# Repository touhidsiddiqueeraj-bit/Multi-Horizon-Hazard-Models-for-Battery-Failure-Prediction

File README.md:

# Multi-Horizon Failure-Risk Models for Battery Failure Prediction

Multi-horizon failure-risk classification for lithium-ion cells: instead of
remaining-useful-life regression, predict whether a cell fails within the next
H cycles. The study's central contribution is a **validity analysis** — apparent
cross-dataset, cross-chemistry transfer is largely a **State-of-Health (SOH)
shortcut**, reproducible by an unfitted threshold rule, not transferable
degradation knowledge. Plus a complete ESP32-S3 embedded deployment.

> **Status.** The deliverable paper is `paper_ieee_access/main_access.pdf`
> (IEEE Access, generated — see [Paper build](#paper-build)). A condensed
> Journal of Energy Storage submission package lives in `paper_jest/`
> (manuscript + supplement). An IEEE Transactions on Reliability submission
> package lives in `paper_tr/` (manuscript, supplement, cover letter,
> checklist, author info). Numbers below are headline values; every number
> in the paper is generated from `results_v2/` — see [Reproduction](#reproduction).

---

## Headline results

- **Within-dataset:** fold-mean AUC 0.90–0.96 across tree ensembles (XGBoost,
  LightGBM, Random Forest) under cell-disjoint evaluation with leakage-free
  (cross-fitted out-of-fold) calibration.
- **SOH ablation (transfer):** ALL-LCO → Severson (141 LFP cells) at H=20 —
  pooled AUC **0.896 with SOH → 0.750 without** (XGBoost); the SOH
  distance-to-threshold rule alone reaches 0.912.
- **Diagnosis vs prognosis:** the label window includes the scoring cycle, so
  with-SOH numbers mix concurrent detection with prediction. Restricting to
  rows scored while SOH > 0.80 gives **0.838** on Severson — the remainder is
  near-threshold ranking, priced by the failure-definition ablation
  (voltage-sag-only relabeling cuts with-SOH transfer 0.90 → 0.72).
- **Battery Archive replication (60 new cells, pre-registered):** with-SOH
  transfer spans 0.77–1.00 pooled AUC, collapsing to 0.36–0.91 outside the
  single-condition HNEI NMC group, where full no-SOH transfer stays ≈0.99
  (narrow stereotyped protocols transfer; diverse ones do not).
- **Calibration:** Platt preserves discrimination best at comparable error;
  isotonic fails under shift; target recalibration repairs ECE but not ranking.
- **Deployment:** three ensembles (900 trees, 26,336 nodes) in a ~372 kB flat
  binary on a $12 ESP32-S3 — under 1 ms per inference for a single
  SRAM-resident model, reproducing `predict_proba()` to within 1.1×10⁻⁶.

Because SOH enters the failure label itself, **all with-SOH transfer numbers
are diagnostic-proximity upper bounds, not pure prognosis** — stated in the
abstract, methods, results, and conclusion.

---

## Datasets

| # | Dataset | Cells | Chemistry | Cycles / rows | Notes |
|---|---------|------:|:---------:|--------------:|-------|
| 1 | NASA 18650 | 37 | LCO | 1,028 cleaned rows (~28/cell) | Randomized profiles, diverse failures |
| 2 | CALCE LCO/CX2 | 7 | LCO | ~8,700 rows | temp + duration unlogged (zero-imputed) |
| 3 | Oxford | 5 | LFP | 320 rows, ~100-cycle spacing | Labels horizon-invariant; Cell5 has 1 positive row |
| 4 | MIT–Stanford Severson | 141 | LFP | ~117k rows, 101–2,237/cell | Fast-charging protocol |
| 5 | HNEI (Battery Archive) | 15 | NMC/LCO | 15,685 rows | 25 °C, single condition, all reach EOL |
| 6 | SNL NCA (Battery Archive) | 18 | NCA | 11,812 rows | 15–35 °C, mixed C-rates |
| 7 | SNL NMC (Battery Archive) | 6 | NMC | 2,997 rows | 15–25 °C |
| 8 | SNL LFP (Battery Archive) | 21 | LFP | 76,293 rows | 15–35 °C, mostly censored (3% prevalence) |

Failure label (composite): SOH ≤ 0.80 **or** average voltage sag beyond 6%
within `[t, t+H)`, H ∈ {10, 20, 30, 50}. The window includes the scoring
cycle and the label stays 1 afterwards. Groups 5–8 come from the Battery
Archive "Cycle Test Data" export (Sept 2026; SNL matrix per Preger et
al. 2020); 60 of 75 downloaded cells admitted under a pre-registered
cleaning rule (`data/ba_audit.csv`, protocol in
`study_materials/batteryarchive_protocol.md`).

---

## Repository layout

```
├── src/                    # Research pipeline (see table below)
├── scripts/                # Paper assembly + gates (make_paper_v2, make_jest, check_overflow)
├── paper/                  # Templates (paper_v2_template_part{1,2}.tex) — EDIT THESE, not the output
├── paper_ieee_access/      # Generated main_access.tex/.pdf + figs/
├── paper_jest/             # JES submission: condensed manuscript + supplement + cover letter
├── results_v2/             # All experiment CSVs, paper_numbers.json, tex_fragments/
│   └── preds/              # Pooled prediction files (~7.5 GB, intentionally untracked)
├── data/                   # Cleaned CSVs (ba_clean.csv 19 MB, ba_audit.csv, *_clean.csv)
├── batteryarchive_cycle_test_data_CSVs/  # Raw BA export + provenance notes
├── esp32_firmware/         # ESP-IDF production firmware
├── arduino_firmware/       # Arduino firmware (web dashboard)
├── pc_validation/          # C-vs-Python validation suite
├── study_materials/        # Protocol, discrepancy note, hazard framework, primer
└── requirements.txt        # Python deps (torch installed separately, CPU or CUDA)
```

### Research modules (`src/`)

| Module | Role | Output |
|---|---|---|
| `pipeline_core.py` | Cell-disjoint splits, OOF calibration, feature sets, loaders | shared |
| `composite_label.py` | Failure labels (`combined`\|`soh_only`\|`volt_only`) | labels |
| `benchmark_cv.py` | Trees: `within` \| `transfer` \| `ablation_tests` | `*_trees.csv`, `transfer_ba.csv`, `*_ba.csv` |
| `gru_cv.py` | GRU (8-unit, 3 seeds): `within` \| `transfer` | `gru_*.csv` |
| `baselines.py` | Distance rule, SOH/cycle/sensor/full logistic regs | `baselines_*.csv` |
| `feature_ablation.py` | 2³−1 grid over {SOH, cycle, sensors} | `feature_ablation*.csv` |
| `faildef_ablation.py` | Single-endpoint relabeling | `faildef_ablation.csv` |
| `same_chem_transfer.py` | Same-chemistry cross-lab controls | `same_chem.csv` |
| `hazard_model.py` | Discrete-time survival model | `hazard_*.csv` |
| `operational_metrics.py` | 20:1 cost model, 10% FPR thresholds | `operational_costs.csv`, `net_benefit_curves.csv` |
| `monotonicity_check.py` | p₁₀≤p₂₀≤p₃₀≤p₅₀ violation rates | `monotonicity.csv` |
| `condition_shift.py` | Leave-condition-out (SNL groups) | `condition_shift.csv` |
| `prognosis_split.py` | All-rows vs SOH>0.80-at-score AUC (no retraining) | `prognosis_split.csv` |
| `loader_batteryarchive.py` + `make_tables_ba.py` | BA loading, audit, BA tables | `data/ba_*.csv`, BA fragments |
| `make_tables_v2.py` | Aggregates everything → `paper_numbers.json` + `tex_fragments/` | 552 keys, 20 fragments |
| `plot_paper_v2.py`, `plot_fig01_v2.py`, `plot_shap.py`, `plot_ba_quality.py`, `plot_fig_deploy_v2.py` | Figures → `paper_ieee_access/figs/` | PNGs |

---

## Reproduction

### Environment

```bash
pip install -r requirements.txt
# torch separately (GRU only): pip install torch --index-url https://download.pytorch.org/whl/cpu
```

### 1. Experiments → CSVs

```bash
cd src
python3 benchmark_cv.py within && python3 benchmark_cv.py transfer
python3 benchmark_cv.py ablation_tests   # includes BA transfer/ablation
python3 gru_cv.py within && python3 gru_cv.py transfer
python3 baselines.py && python3 feature_ablation.py && python3 faildef_ablation.py
python3 same_chem_transfer.py
python3 hazard_model.py within && python3 hazard_model.py transfer
python3 operational_metrics.py && python3 monotonicity_check.py
python3 condition_shift.py && python3 prognosis_split.py
```

> ⚠️ **Two load-bearing contracts.** (1) Keep `n_jobs=1` for Random Forest
> (≤2 for boosters) — `n_jobs=4` deadlocks under nested CV. (2)
> `make_composite_fail_in_H` returns labels in the *input frame's* row order —
> `reset_index(drop=True)` frames before positional slicing.

### 2. Aggregate → assemble

```bash
cd src && python3 make_tables_v2.py        # → results_v2/paper_numbers.json + tex_fragments/
cd .. && python3 scripts/make_paper_v2.py  # fills every @@TOKEN@@ (fails loudly on gaps)
```

### 3. Compile (IEEE Access)

```bash
export TEXMFCNF=/usr/share/texmf-dist/web2c:
export TEXINPUTS=<texflow>/data/ieee//:$PWD/paper_ieee_access/figs//:/usr/share/texmf-dist/tex//:
export TEXFONTS=<texflow>/data/ieee//:/usr/share/texmf-dist/fonts//:
export FONTMAP=<texflow>/data/ieee//:
cd paper_ieee_access && pdflatex -progname=pdflatex main_access.tex  # twice
```

The `-progname` flag and `TEXMFCNF` are required (AppImage `argv[0]` breaks
kpathsea); xelatex does not work. Never hand-edit `main_access.tex` — it
regenerates on every assembly.

### 4. JES package

```bash
python3 scripts/make_jest.py --condensed   # main_condensed + supplement (.tex/.pdf)
```

### 5. Gates (must pass before commit)

```bash
python3 scripts/check_overflow.py paper_ieee_access/main_access.pdf   # CLEAN if max ≤ 0.94
python3 scripts/check_overflow.py paper_jest/main_condensed.pdf
```

Zero `pdflatex` errors, zero undefined refs/cites, no leftover `@@TOKENS@@`,
no dangling `\ref`s (check both docs after any template edit).

---

## Paper outputs

| File | What |
|---|---|
| `paper_ieee_access/main_access.pdf` | Full paper, 23pp IEEE Access (generated) |
| `paper_jest/main_condensed.pdf` | JES submission manuscript, 7 tables + 3 figs (generated) |
| `paper_jest/supplement.pdf` | 15 tables + 11 figs omitted for length (generated) |
| `paper_jest/main_jest.pdf` | Full-length elsarticle port (record only, not for submission) |
| `paper_jest/{highlights.txt,cover_letter.txt}` | Submission files (author details are placeholders) |

JES guidance is ideally ≤6,000 words / 8–10 floats; the condensed manuscript
is ~7,700 words at exactly 10 floats — disclosed in the cover letter with a
further-condensation offer. See `paper_jest/README.md`.

---

## Firmware & validation (summary)

Three tree ensembles export to one ~372 kB flat binary (`scripts/export_esp32_models.py`),
run by a hand-written C tree walker on ESP32-S3 (ESP-IDF production firmware in
`esp32_firmware/`, Arduino dashboard variant in `arduino_firmware/`).
Three validation stages (Python walker → x86 C binary → on-device) must agree
within 1e-5 (`pc_validation/`, `make validate`). Sensor wiring: INA219 +
DS3231 on I2C (GPIO8/9), DS18B20 on OneWire (GPIO10), voltage divider on ADC
GPIO1. See `esp32_firmware/` and `arduino_firmware/README.md` for build/flash
details (`run_all.sh` runs the end-to-end deployment pipeline).

> Note: the paper's prototype-wiring figure was removed (hardware unbuilt);
> on-device measurement claims in §III-M are retained as stated — verify
> against hardware before citing them externally.

---

## Methodological contracts (read before extending)

- **Cell-disjoint everything.** Train, calibration, and test never share a
  cell. Calibrators fit only on cross-fitted out-of-fold source scores.
- **Cell = experimental unit.** Headline evidence is cell-level bootstrap CIs;
  DeLong p-values are cycle-level, pseudoreplication-inflated, secondary only.
- **Oxford caveats.** 5 cells at ~100-cycle spacing → labels identical across
  horizons (pooled detection, not horizon-resolved); Cell5 has one positive row.
- **SNL LFP** is mostly censored (3% prevalence) — supporting evidence only.
- **Zero-imputation confound.** Missing current/temperature columns are
  zero-filled (CALCE + BA); a constant-zero column acts as a dataset identifier
  in pooled training — conclusions rest on the common unit-safe feature set.
- **`results_v2/preds/` (~7.5 GB) is intentionally untracked.** Do not commit
  it; the CSVs + `paper_numbers.json` reproduce every table.

---

## Citation

```bibtex
@inproceedings{siddiquee2026multi,
  title={Multi-Horizon Hazard Models for Battery Failure Prediction: Within-Dataset Reliability and Cross-Chemistry Transferability},
  author={Siddiquee, Hussain Touhid and Islam, Syeda Salsabil and Islam, Ariya Jasimul and Eshica, Chowdhury Farzana Hoque},
  year={2026}
}
```

Key data sources: NASA Ames Prognostics Repository (Saha & Goebel 2007),
CALCE (Univ. Maryland), Oxford Battery Degradation Dataset 1 (Birkl & Howey
2017), Severson et al., *Nature Energy* 2019 (+ Attia et al., *Nature* 2020),
Battery Archive "Cycle Test Data" (HNEI + SNL; SNL matrix per Preger et
al., *J. Electrochem. Soc.* 2020). Full 25-entry bibliography is in the paper.

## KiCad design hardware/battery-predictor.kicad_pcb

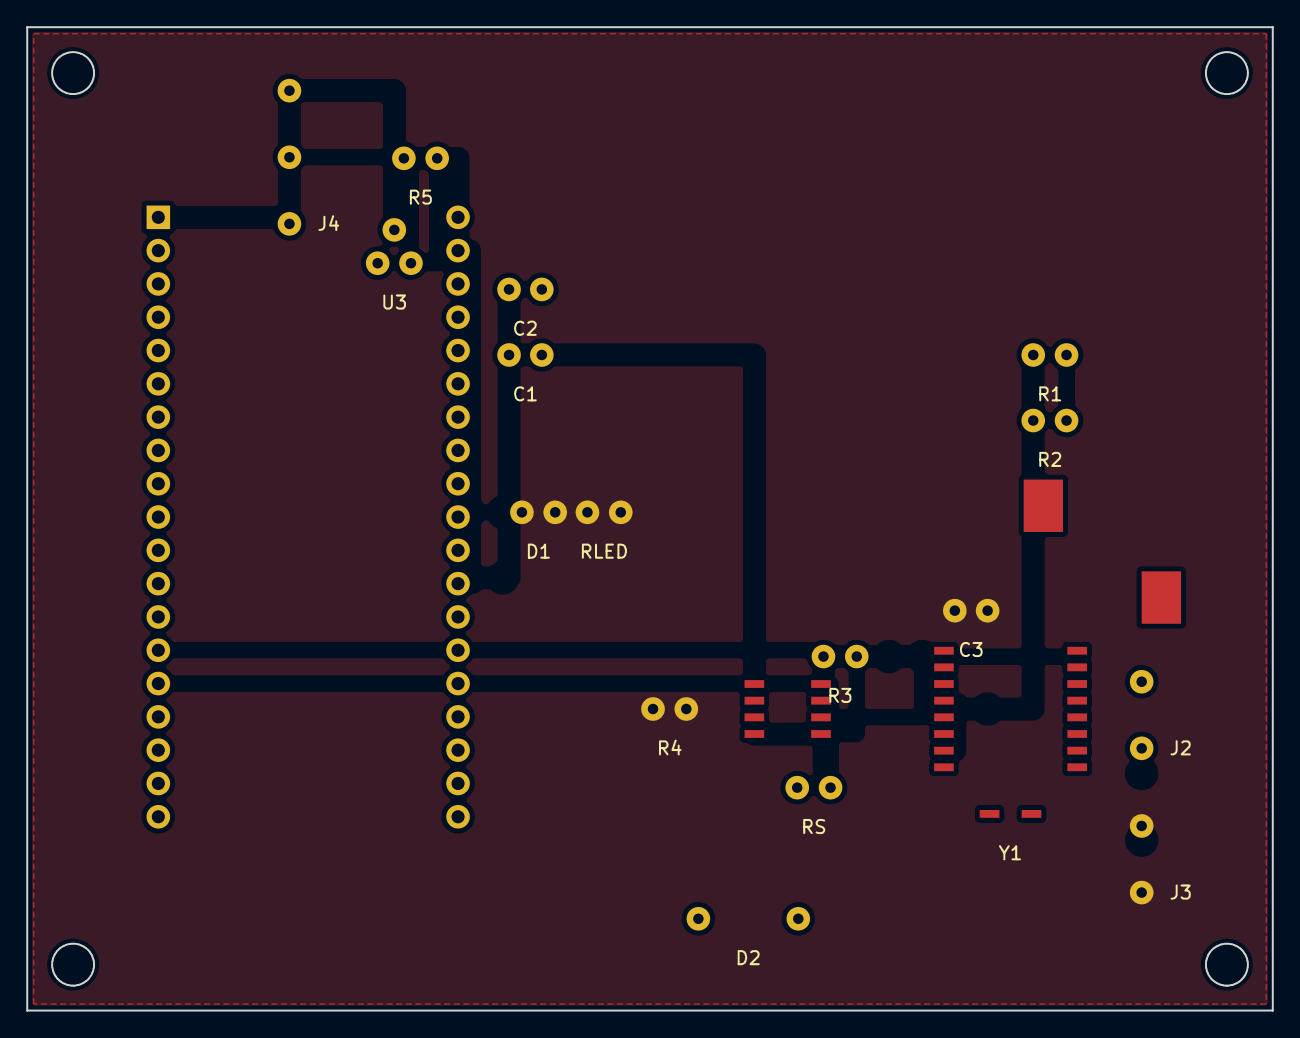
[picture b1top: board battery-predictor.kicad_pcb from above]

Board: 2 copper layers, 95.0 x 75.0 mm, 21 parts (0 on the bottom side), 12 nets, no tracks yet.

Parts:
BT1: CR1220; BatteryHolder_Keystone_3001_1xCR1220
C1, C3: 100nF; C_Radial_D5.0mm_P2.5mm
C2: 100uF; C_Radial_D5.0mm_P2.5mm
D1: GREEN; LED_D3.0mm
D2: 1N4148; D_DO-35_SOD27_P7.62mm_Horizontal
J1: ESP32-S3-DevKitC-1; PinHeader_2x19_P2.54mm_Vertical
J2: BAT_IN; TerminalBlock_Phoenix_MKDS-1,5-2-5.08_1x02_P5.08mm_Horizont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
J3: LOAD; TerminalBlock_Phoenix_MKDS-1,5-2-5.08_1x02_P5.08mm_Horizont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
J4: TEMP_PROBE; TerminalBlock_Phoenix_MKDS-1,5-3-5.08_1x03_P5.08mm_Horizont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
R1, R2: 10k; R_Axial_DIN0207_L6.3mm_D2.5mm_P2.54mm_Vertical
R3, R4, R5: 4.7k; R_Axial_DIN0207_L6.3mm_D2.5mm_P2.54mm_Vertical
RLED: 1k; R_Axial_DIN0207_L6.3mm_D2.5mm_P2.54mm_Vertical
RS: 0.1 1W; R_Axial_DIN0207_L6.3mm_D2.5mm_P2.54mm_Vertical
U1: INA219; SOIC-8_3.9x4.9mm_P1.27mm
U2: DS3231; SOIC-16W_7.5x10.3mm_P1.27mm
U3: DS18B20; TO-92_Inline
Y1: 32.768kHz; Crystal_SMD_3.2x1.5mm_HandSoldering

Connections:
3V3: C1.1, C2.1, C3.1, J1.1, J1.21, J4.1, R3.1, R4.1, R5.1, RLED.1, U1.1, U2.2, U3.3
BAT_IN: D2.1, J2.1
GND: BT1.2, C1.2, C2.2, C3.2, D1.2, J1.11, J2.2, J3.2, J4.3, R2.2, U1.2, U2.10, U3.1
LED: D1.1, RLED.2
RTC_VBAT: BT1.1, U2.9
RTC_XTAL: U2.7, U2.8, Y1.1, Y1.2
SCL: J1.15, J1.24, R4.2, U1.4, U2.6
SDA: J1.14, J1.23, R3.2, U1.3, U2.5
TEMP_DQ: J1.25, J4.2, R5.2, U3.2
VBAT_DIV: J1.7, R1.2, R2.1
VIN+: D2.2, R1.1, RS.1, U1.6
VIN-: J3.1, RS.2, U1.5

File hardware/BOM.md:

# BOM — Battery Predictor Sensor Shield

## Required Components

| Ref | Part | Package | Qty | Notes |
|-----|------|---------|-----|-------|
| R1, R2 | 10kΩ 1% | Axial THT (or 0805) | 2 | Voltage divider |
| R3, R4, R5 | 4.7kΩ 5% | Axial THT | 3 | I2C + OneWire pullups |
| RS | 0.1Ω 1% 1W | Axial THT (or 2512) | 1 | Current shunt |
| RLED | 1kΩ 5% | Axial THT | 1 | LED current limit |
| C1, C3 | 100nF ceramic | 5mm pitch THT | 2 | Bypass caps |
| C2 | 100μF 16V electrolytic | 5mm radial THT | 1 | Bulk decoupling |
| D1 | LED 3mm green | 3mm THT | 1 | Power indicator |
| U1 | INA219 | SOIC-8 | 1 | Current sensor |
| U2 | DS3231 | SOIC-16W | 1 | RTC |
| U3 | DS18B20 | TO-92 | 1 | Temperature sensor |
| Y1 | 32.768kHz crystal | 3.2×1.5mm SMD | 1 | DS3231 timekeeping |
| BT1 | CR1220 holder | SMD | 1 | RTC backup battery |
| J1 | 2×19 female header | 2.54mm pitch | 1 | ESP32-S3-DevKitC-1 connector |
| J2, J3 | 2-pin screw terminal | 5.08mm pitch | 2 | Battery in, load out |
| J4 | 3-pin screw terminal | 5.08mm pitch | 1 | External temp probe |

## Also Needed

| Item | Notes |
|------|-------|
| ESP32-S3-DevKitC-1 | Plugs into J1 |
| CR1220 battery | RTC backup |
| 18650 battery (or test cell) | Battery under test |
| DS18B40 probe (optional) | External temp sensor |
| Jumper wires or 2.54mm header pins | If not using DevKit directly |

## Optional

| Item | Notes |
|------|-------|
| 4× M3 nylon standoffs + screws | Mounting |

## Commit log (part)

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2026-06-27 Apply patch: firmware fixes, documentation corrections, build config updates
    - INA219: 320mA -> 2A range (prevents saturation on real 18650 discharge)
    - SOH calibrator: fix divisor to use actual baseline count
    - Arduino tree walk: depth cap -> while loop (no depth limit)
    - Comparison precision: float32 for XGBoost, float64 cast for LightGBM/RF
    - P_THRESHOLD command: now implemented in ESP32 UART handler
    - ARCHITECTURE.md/README.md: corrected AUC values, binary format details
